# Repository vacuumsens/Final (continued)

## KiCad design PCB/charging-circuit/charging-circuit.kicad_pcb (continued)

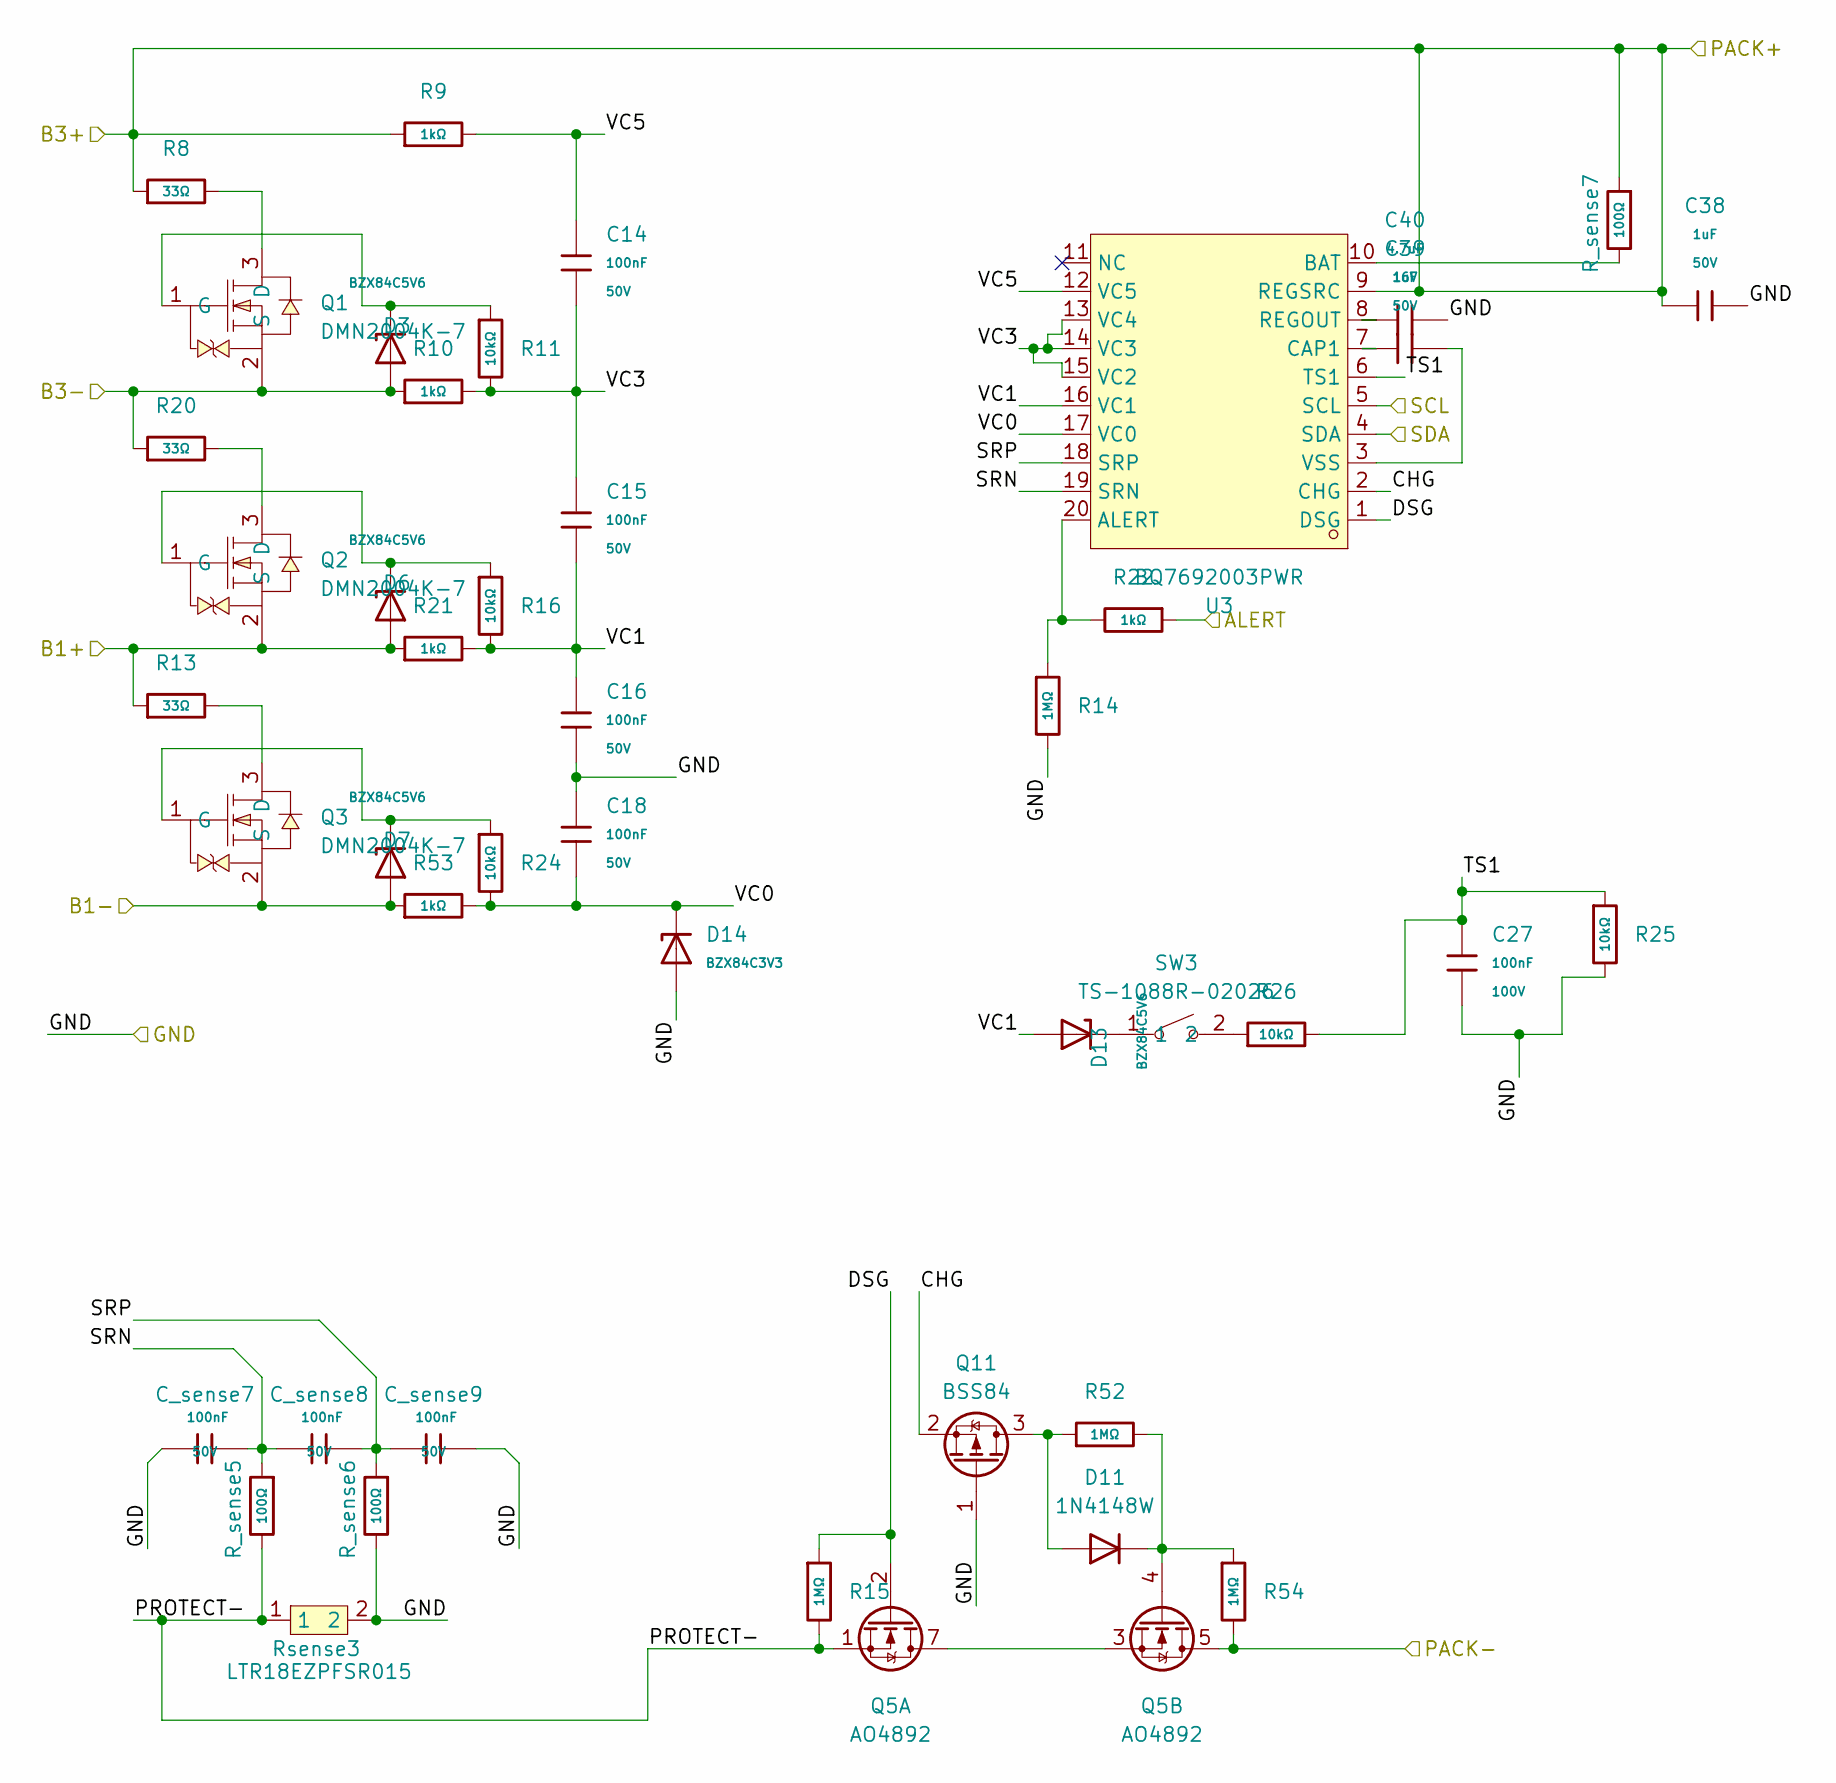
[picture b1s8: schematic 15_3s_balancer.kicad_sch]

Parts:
C14, C15, C16, C18: 100nF; C_0603; Voltage Rated 50V; Tolerance ±10%; Part CC0603KRX7R9BB104; LCSC C14663
C27: 100nF; C_0805; Voltage Rated 100V; Tolerance ±10%; Part CL21B104KCFNNNE; LCSC C28233
C38, C39: 1uF; C_0603; Voltage Rated 50V; Tolerance ±10%; Part CL10A105KB8NNNC; LCSC C15849
C40: 4.7uF; C_0603; Voltage Rated 16V; Tolerance ±10%; Part CL10A475KO8NNNC; LCSC C19666
C_sense7, C_sense8, C_sense9: 100nF; C_0603; Voltage Rated 50V; Tolerance ±10%; Part CC0603KRX7R9BB104; LCSC C14663
D3, D6, D7, D13: BZX84C5V6; D_SOT-23; Part BZX84C5V6; LCSC C19077469
D11: 1N4148W; D_SOD-123
D14: BZX84C3V3; D_SOT-23; Zener Voltage (Range) 3.1V~3.5V; Zener Voltage (Nom) 3.3V; Part BZX84C3V3; LCSC C19077467
Q1, Q2, Q3: DMN2004K-7; SOT-23-3_L3.0-W1.7-P0.95-LS2.9-BR; MPN DMN2004K-7; LCSC Part C75285
Q5: AO4892; SOIC-8_3.9x4.9mm_P1.27mm; LCSC Part C357830
Q11: BSS84; SOT-23; LCSC Part C82079
R8, R13, R20: 33Ω; R_0805; Overload Voltage (Max) 150V; Tolerance ±1%; Part 0805W8F330JT5E; LCSC C17634
R9, R10, R21, R22, R53: 1kΩ; R_0805; Overload Voltage (Max) 150V; Tolerance ±1%; Part 0805W8F1001T5E; LCSC C17513
R11, R16, R24, R25, R26: 10kΩ; R_0805; Overload Voltage (Max) 150V; Tolerance ±1%; Part 0805W8F1002T5E; LCSC C17414
R14: 1MΩ; R_0805; Overload Voltage (Max) 150V; Tolerance ±1%; Part 0805W8F1004T5E; LCSC C17514
R15, R52, R54: 1MΩ; R_0603; Overload Voltage (Max) 75V; Tolerance ±1%; Part 0603WAF1004T5E; LCSC C22935
R_sense5, R_sense6, R_sense7: 100Ω; R_0603; Overload Voltage (Max) 75V; Tolerance ±1%; Part 0603WAF1000T5E; LCSC C22775
Rsense3: LTR18EZPFSR015; R0612; LCSC Part C510175
SW3: TS-1088R-02026; SW-SMD_L3.9-W3.0-P4.45; LCSC Part C455280
U3: BQ7692003PWR; TSSOP-20_L6.5-W4.4-P0.65-LS6.4-BL; MPN BQ7692003PWR; LCSC Part C601650

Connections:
/3S Balancer/ALERT: R22.1
/3S Balancer/B1+: D6.1, Q2.2 (S), R13.1, R21.1; also elsewhere on the board
/3S Balancer/B3-: D3.1, Q1.2 (S), R10.1, R20.1; also elsewhere on the board
/3S Balancer/CHG: Q11.2 (S), U3.2 (CHG)
/3S Balancer/DSG: Q5.2 (G1), R15.1, U3.1 (DSG)
/3S Balancer/PROTECT-: Q5.1 (S1), R15.2, R_sense5.2, Rsense3.1
/3S Balancer/SRN: C_sense7.2, C_sense8.1, R_sense5.1, U3.19 (SRN)
/3S Balancer/SRP: C_sense8.2, C_sense9.1, R_sense6.1, U3.18 (SRP)
/3S Balancer/TS1: C27.1, R25.1, R26.2, U3.6 (TS1)
/3S Balancer/VC0: C18.2, D14.3, R24.2, R53.2, U3.17 (VC0)
/3S Balancer/VC1: C15.2, C16.1, D13.1, R16.2, R21.2, U3.16 (VC1)
/3S Balancer/VC3: C14.2, C15.1, R10.2, R11.2, U3.13 (VC4), U3.14 (VC3), U3.15 (VC2)
/3S Balancer/VC5: C14.1, R9.2, U3.12 (VC5)
/3S IC/BAT+: C38.1, R8.1, R9.1, R_sense7.1, U3.9 (REGSRC); also elsewhere on the board
/GND: C16.2, C18.1, C27.2, C38.2, C40.2, C_sense7.1, C_sense9.2, D7.1, D14.1, Q3.2 (S), Q5.5 (D2), Q5.6 (D2), Q11.1 (G), R14.2, R25.2, R53.1, R54.2, R_sense6.2, Rsense3.2; also elsewhere on the board
/GPIO2/SDA1: U3.4 (SDA); also elsewhere on the board
/GPIO3/SCL1: U3.5 (SCL); also elsewhere on the board
unnamed: D11.2 (A), Q11.3 (D), R52.1
unnamed: D11.1 (K), Q5.4 (G2), R52.2, R54.1
unnamed: D13.3, SW3.1
unnamed: Q1.3 (D), R8.2
unnamed: D3.3, Q1.1 (G), R11.1
unnamed: Q2.3 (D), R20.2
unnamed: D6.3, Q2.1 (G), R16.1
unnamed: Q3.3 (D), R13.2
unnamed: D7.3, Q3.1 (G), R24.1
unnamed: Q5.3 (S2), Q5.7 (D1), Q5.8 (D1)
unnamed: R26.1, SW3.2
unnamed: R14.1, R22.2, U3.20 (ALERT)
unnamed: R_sense7.2, U3.10 (BAT)
unnamed: C39.1, U3.7 (CAP1)
unnamed: C40.1, U3.8 (REGOUT)
unnamed: C39.2, U3.3 (VSS)

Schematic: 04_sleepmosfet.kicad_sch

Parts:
C65: 100nF; C_0603; Voltage Rated 50V; Tolerance ±10%; Part CC0603KRX7R9BB104; LCSC C14663
Q21, Q24, Q25, Q26: 2N7002; SOT-23-3_L2.9-W1.3-P1.90-LS2.4-BR; LCSC Part C8545
Q22, Q27, Q28: CJQ4435; SOP-8_L5.0-W4.0-P1.27-LS6.2-BL; LCSC Part C114076
R6: 3362P-1-204; RES-ADJ-TH_3P-L7.1-W6.9-P2.50-L_3362P; MPN 3362P-1-204; LCSC Part C118941
R37, R38, R41, R43, R47: 10kΩ; R_0603; Overload Voltage (Max) 75V; Tolerance ±1%; Part 0603WAF1002T5E; LCSC C25804
R46, R48, R49: 100kΩ; R_0603; Overload Voltage (Max) 75V; Tolerance ±1%; Part 0603WAF1003T5E; LCSC C25803
RPROG9, RPROG10: 1kΩ; R_0603; Overload Voltage (Max) 75V; Tolerance ±1%; Part 0603WAF1001T5E; LCSC C21190
U19: TPL5110DDCT; TSOT-23-6_L2.9-W1.6-P0.95-LS2.8-BR; LCSC Part C125830

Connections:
/DSUB+RS232/DSUB3.3V: Q22.1 (S), Q22.2 (S), Q22.3 (S), R43.2, R46.1, U19.1 (VDD), U19.6 (EN/ONE_SHOT); also elsewhere on the board
/DSUB+RS232/DSUB12V: Q28.5 (D), Q28.6 (D), Q28.7 (D), Q28.8 (D), R49.2; also elsewhere on the board
/GND: C65.2, Q21.2 (S), Q24.2 (S), Q25.2 (S), Q26.2 (S), R6.2, R37.2, R38.2, R41.1, R49.1, RPROG9.2, RPROG10.2, U19.2 (GND); also elsewhere on the board
/GPIO23: Q21.1 (G), R41.2; also elsewhere on the board
/LM2596 3V3 BUCK/LM2596_VIN: Q27.1 (S), Q27.2 (S), Q27.3 (S), Q28.1 (S), Q28.2 (S), Q28.3 (S), R47.2, R48.2; also elsewhere on the board
/SLEEPMOSFET/5EN: Q27.5 (D), Q27.6 (D), Q27.7 (D), Q27.8 (D), RPROG10.1; also elsewhere on the board
/SLEEPMOSFET/SLPDRV: Q24.1 (G), Q25.1 (G), R38.1, U19.5 (DRV)
/SLEEPMOSFET/SLPSIG: C65.1, Q22.5 (D), Q22.6 (D), Q22.7 (D), Q22.8 (D), R37.1, RPROG9.1, U19.4 (DONE)
unnamed: Q21.3 (D), Q22.4 (G), R43.1
unnamed: Q24.3 (D), Q26.1 (G), R46.2
unnamed: Q25.3 (D), Q27.4 (G), R47.1
unnamed: Q26.3 (D), Q28.4 (G), R48.1
unnamed: R6.3, U19.3 (DELAY/M_DRV)

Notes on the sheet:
n, pmos driver for enable pin of lmk2596 5 volts
Battery can still charge while timer off DONE = rising edge, turn off mosfet and circuit power for sleep timer DONE = low, circuit power on
timing resistor 20k for around 2 minutes
Module: SLEEPMOSFET Move the matching boxed circuit here from charging-circuit.flat-backup.kicad_sch. Use global labels or hierarchical pins for any net that must connect outside this sheet. Suggested nets: SLEEPGND, SLEEPSIG, SLEEPVSYS
n, pmos driver for raspi to tpl5110 side (3.3 Volts NOT 12)
n,n,pmos driver for 12Volts (directly from battery)

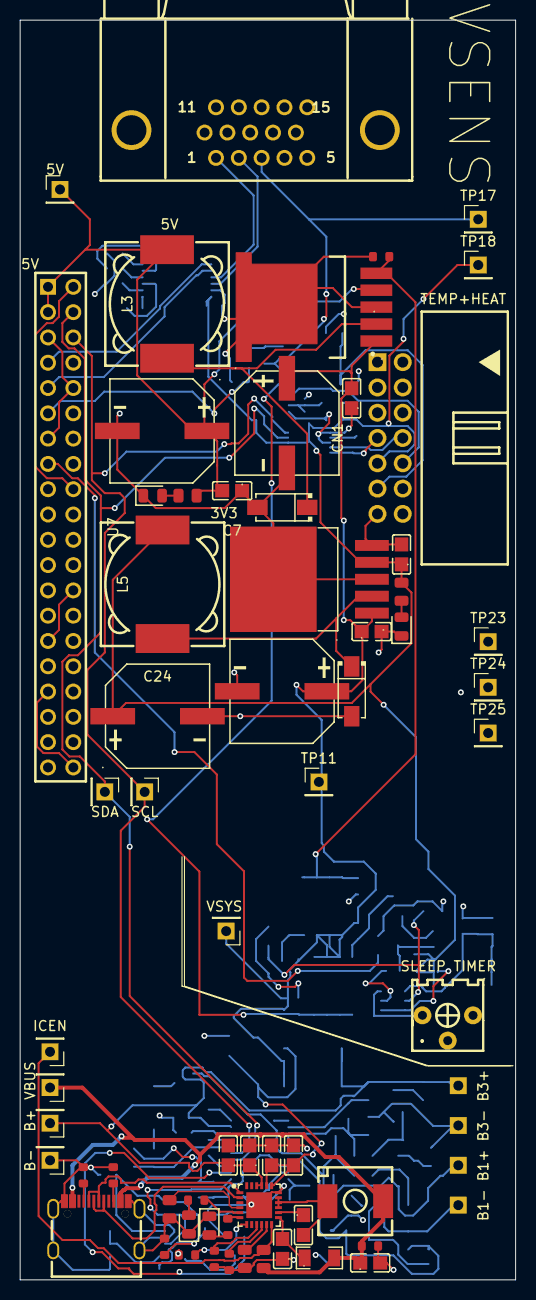
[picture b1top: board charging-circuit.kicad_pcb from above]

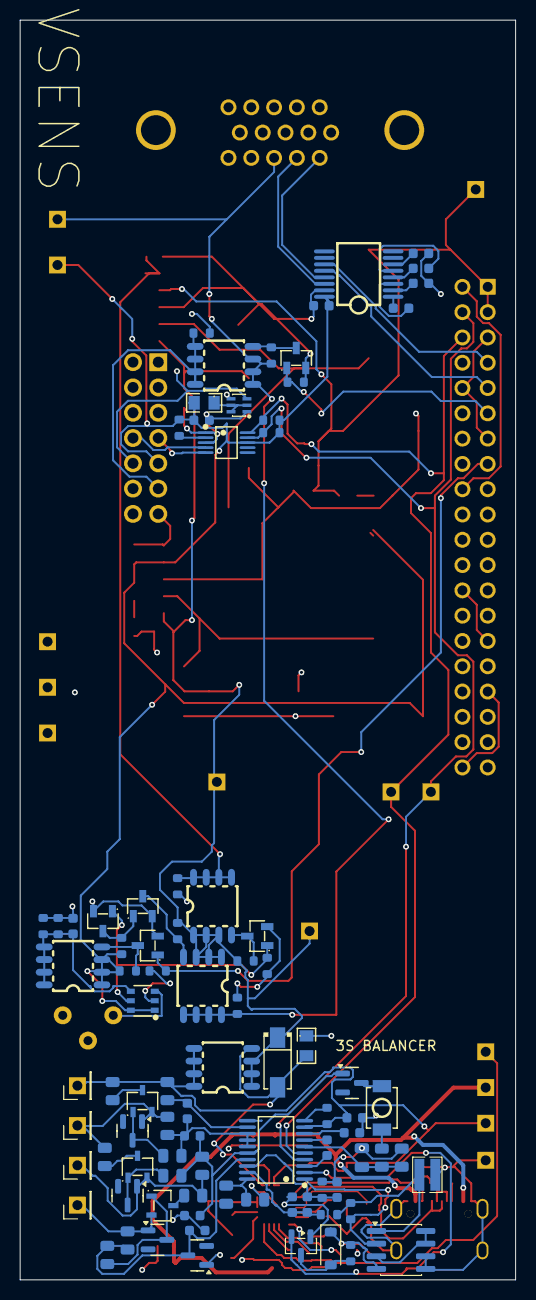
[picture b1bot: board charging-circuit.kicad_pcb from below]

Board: 4 copper layers, 49.8 x 126.5 mm, 150 parts (88 on the bottom side), 87 nets.

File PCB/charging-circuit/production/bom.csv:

Designator,Footprint,Quantity,Value,LCSC Part #
"_15, _14, _13, _12, _11, _10, _9, _8, _7, _6, _5, _4, _3, _2, ",,15,,
"C10, C11, C12, C8",C0805,4,10uf,C84416
"C13, C14, C15, C16, C18, C22, C29, C33, C35, C36, C65, C_SENSE7, C_SENSE8, C_SENSE9",C_0603,14,100nF,C14663
"C19, C2, C3, C6, C7",C0805,5,100nf,C1711
C21,CAP-SMD_BD10.0-L10.3-W10.3-FD,1,330uf,C19606
"C23, C24, C25",CAP-SMD_BD10.0-L10.3-W10.3-LS11.0-FD,3,470uf,C3351
C27,C_0805,1,100nF,C28233
"C38, C39",C_0603,2,1uF,C15849
"C4, C5",C0805,2,22uf,C45783
C40,C_0603,1,4.7uF,C19666
CN1,IDC-TH_14P-P2.54_ZHOURI_DC3-2.54-14PAL,1,DC3-2.54-14PAL,C5156673
"D1, D2, D5",SMA_L4.4-W2.8-LS5.4-R-RD,3,SS54_C22452,C22452
"D10, D12, D9",D_0805,3,Green,C2297
D11,D_SOD-123,1,1N4148W,
"D13, D3, D6, D7",D_SOT-23,4,BZX84C5V6,C19077469
D14,D_SOT-23,1,BZX84C3V3,C19077467
D8,D_0805,1,Red,C84256
DSUB2,DSUB-TH_DS1038-15FBNSIA74-0CC,1,DS1038-15FBNSIA74-0CC,C75754
L1,IND-SMD_L7.1-W6.5-P5.60,1,SPM6530T-2R2M,C76855
"L3, L5",IND-SMD_L12.3-W12.3,2,SMDRI127-330MT,C9400
"Q1, Q2, Q3",SOT-23-3_L3.0-W1.7-P0.95-LS2.9-BR,3,DMN2004K-7,C75285
Q11,SOT-23,1,BSS84,C82079
"Q14, Q21, Q24, Q25, Q26",SOT-23-3_L2.9-W1.3-P1.90-LS2.4-BR,5,2N7002,C8545
"Q17, Q18, Q22, Q27, Q28",SOP-8_L5.0-W4.0-P1.27-LS6.2-BL,5,CJQ4435,C114076
Q23,SOT-363-6_L2.2-W1.3-P0.65-LS2.1-BL,1,currentmirror,C41375126
Q5,SOIC-8_3.9x4.9mm_P1.27mm,1,AO4892,C357830
R1,R0805,1,0805W8F2553T5E,C17578
"R10, R21, R22, R53, R9",R_0805,5,1kΩ,C17513
"R11, R16, R24, R25, R26",R_0805,5,10kΩ,C17414
R12,R_0805,1,62kΩ,C17783
"R13, R20, R8",R_0805,3,33Ω,C17634
R14,R_0805,1,1MΩ,C17514
"R15, R52, R54",R_0603,3,1MΩ,C22935
"R18, R19",R_0805,2,51kΩ,C17737
"R2, R3",R_0805,2,4.7kΩ,C17673
"R31, R32, R33, R40, R44, R45",R_0603,6,5.1kΩ,C23186
"R37, R38, R39, R41, R43, R47, R50",R_0603,7,10kΩ,C25804
R4,R1206,1,0.5ohm,C25340
"R46, R48, R49, R51",R_0603,4,100kΩ,C25803
R5,R0805,1,100k,C25611
R6,RES-ADJ-TH_3P-L7.1-W6.9-P2.50-L_3362P,1,3362P-1-204,C118941
"RPROG10, RPROG11, RPROG12, RPROG13, RPROG14, RPROG15, RPROG8, RPROG9",R_0603,8,1kΩ,C21190
RSENSE3,R0612,1,LTR18EZPFSR015,C510175
"R_SENSE5, R_SENSE6, R_SENSE7",R_0603,3,100Ω,C22775
SW3,SW-SMD_L3.9-W3.0-P4.45,1,TS-1088R-02026,C455280
TP10,PinHeader_1x01_P2.54mm_Vertical,1,VSYS,
TP15,PinHeader_1x01_P2.54mm_Vertical,1,SDA,
TP16,PinHeader_1x01_P2.54mm_Vertical,1,SCL,
TP17,PinHeader_1x01_P2.54mm_Vertical,1,12VOUT,
TP18,PinHeader_1x01_P2.54mm_Vertical,1,3V3,
TP19,PinHeader_1x01_P2.54mm_Vertical,1,TX,
"TP2, TP3, TP4, TP5, TP9",PinHeader_1x01_P2.54mm_Vertical,5,TestPoint,
TP20,PinHeader_1x01_P2.54mm_Vertical,1,RX,
TP21,PinHeader_1x01_P2.54mm_Vertical,1,5V,
TP6,PinHeader_1x01_P2.54mm_Vertical,1,BAT-,
TP7,PinHeader_1x01_P2.54mm_Vertical,1,Bat+,
TP8,PinHeader_1x01_P2.54mm_Vertical,1,VBUS,
U1,VQFN-24_L4.0-W4.0-P0.50-BL-EP2.5,1,IP2326,C2832094
U10,SSOP-16_L6.2-W5.3-P0.65-LS7.8-BL,1,MAX3232CDBR,C7257
U12,MSOP-10_L3.0-W3.0-P0.50-LS5.0-BL,1,ADS1115IDGSR,C37593
U19,TSOT-23-6_L2.9-W1.6-P0.95-LS2.8-BR,1,TPL5110DDCT,C125830
U2,TDFN-8_L2.0-W2.0-P0.50-BL-EP1.2,1,MAX17048G+T10,C2682616
U3,TSSOP-20_L6.5-W4.4-P0.65-LS6.4-BL,1,BQ7692003PWR,C601650
U4,TO-263-5_L10.2-W8.6-P1.70-LS14.4-TL,1,LM2596SX-3.3,C5186052
U6,TO-263-5_L10.2-W8.9-P1.70-TL,1,LM2596SX-5.0/NOPB,C10002
U7,HDR-TH_40P-P2.54-V-F-R2-C20-S2.54,1,2.54-2*20,C2977589
USBC1,USB-C_SMD-TYPE-C-31-M-12_1,1,TYPE-C-31-M-12,C165948

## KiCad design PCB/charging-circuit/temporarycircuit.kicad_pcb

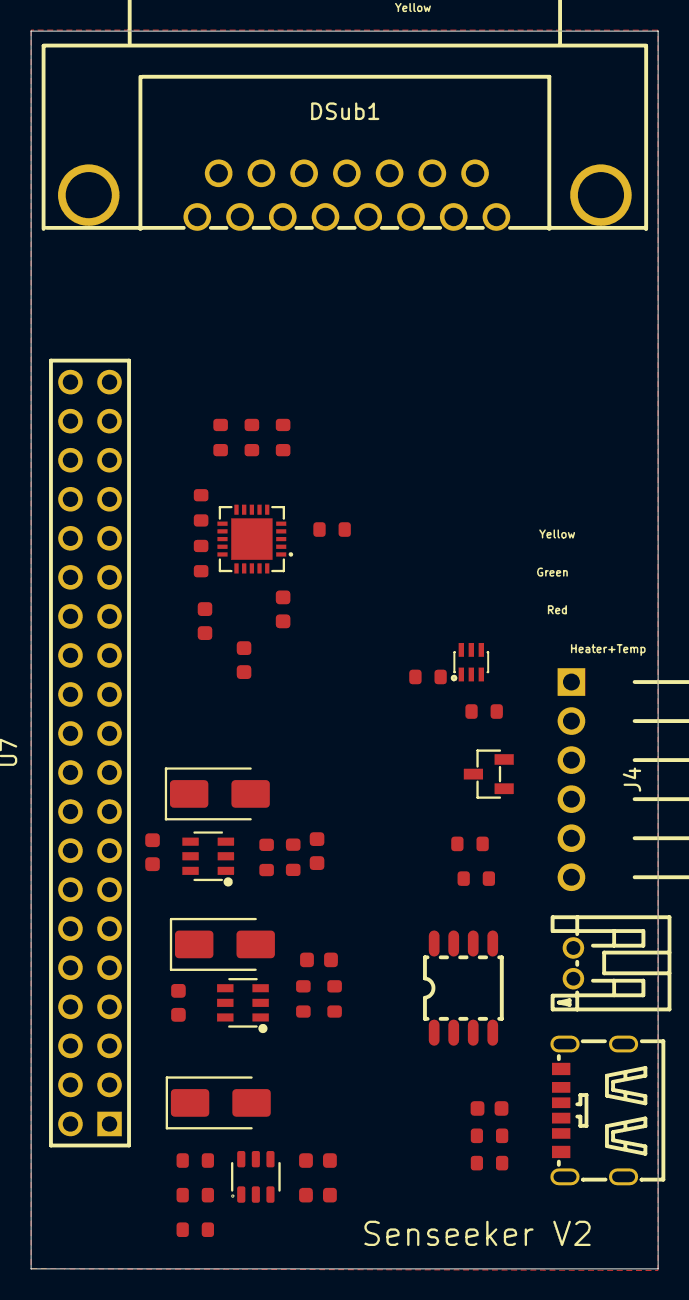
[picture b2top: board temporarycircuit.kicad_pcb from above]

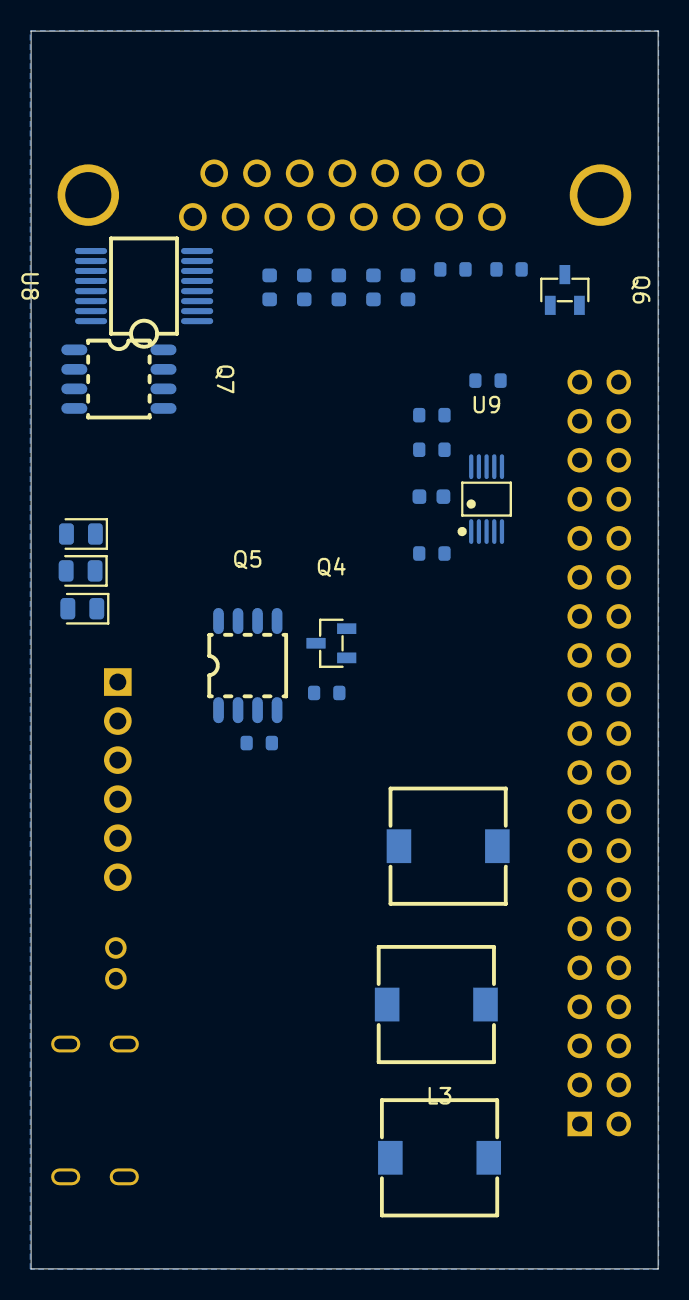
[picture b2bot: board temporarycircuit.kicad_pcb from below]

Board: 2 copper layers, 40.8 x 80.5 mm, 70 parts (26 on the bottom side), 53 nets, no tracks yet.

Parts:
C1, C6: 4.7uF; C_0603
C2, C12, C17, C18, C19, C20, C21: 100nF; C_0603
C3, C4, C5, C7, C10, C11: 22uF; C_0603
C8: 10uF; C_0603
D1: Red; D_0805
D2: Yellow; D_0805
D3: Green; D_0805
D4, D5, D6: SS34; D_SMA
DSub1: DS1037-15FNAKT74-0CC; DSUB-TH_DS1037-15FNAKT74-0CC
J1: USB_C_Receptacle_PowerOnly_6P; TYPE-C-SMD_TYPE-C-6P
J4: Heater+TempPins; HDR-TH_6P-P2.54-H-M-W10.0
L1, L2, L3: 22uH; IND-SMD_L7.5-W7.5
Q1, Q4, Q6: 2N7002; SOT-23-3_L2.9-W1.3-P1.90-LS2.4-BR
Q2, Q5, Q7: CJQ4435; SOP-8_L5.0-W4.0-P1.27-LS6.2-BL
Q3: currentmirror; SOT-363-6_L2.2-W1.3-P0.65-LS2.1-BL
R1, R2, R12, R13, R21: 5.1kΩ; R_0603
R3: 3kΩ; R_0603
R4: 20kΩ; R_0603
R5, R14, R15, R16: 10kΩ; R_0603
R6, R7, R11: 470Ω; R_0603
R8: 91kΩ; R_0603
R9: 4.7kΩ; R_0603
R10: 22kΩ; R_0603
R18: 6.8kΩ; R_0603
R19: 2kΩ; R_0603
R20: 2.2kΩ; R_0603
R22: 100Ω; R_0603
R23: 240kΩ; R_0603
RPROG1, RPROG4, RPROG5, RPROG6: 1kΩ; R_0603
RPROG3: 10kΩ; R_0603
U2, U3, U6: MT3608; SOT-23-6_L2.9-W1.6-P0.95-LS2.8-BL
U4: MCP73871; QFN-20_L4.0-W4.0-P0.5-BL-EP
U5: Battery Input; CONN-TH_S2B-PH-K-S-GW
U7: 2.54-2*20; HDR-TH_40P-P2.54-V-F-R2-C20-S2.54
U8: MAX3232CDBR; SSOP-16_L6.2-W5.3-P0.65-LS7.8-BL
U9: ADS1115IDGSR; MSOP-10_L3.0-W3.0-P0.50-LS5.0-BL

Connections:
/3.3V: C11.2, C21.1, D6.1, Q5.1 (S), Q5.2 (S), Q5.3 (S), R16.2, R18.1, U8.16 (VCC)
/5 Vout: C4.2, D5.1, R10.1, U7.2, U7.4
/12V: C3.2, D4.1, Q2.1 (S), Q2.2 (S), Q2.3 (S), Q7.1 (S), Q7.2 (S), Q7.3 (S), R8.1, R14.2, R15.2
/A0: J4.5, U9.4 (AIN0)
/A1: J4.6, U9.5 (AIN1)
/Address: R22.2, U9.1 (ADDR)
/GPIO3/SCL1: R12.2, R21.2, U7.5, U9.9 (SDA), U9.10 (SCL)
/GPIO14/TXD0: U7.8, U8.11 (DIN1)
/GPIO15/RXD0: U7.10, U8.12 (ROUT1)
/GPIO18/PCM.CLK: Q1.1 (G), U7.12
/GPIO23: Q6.1 (G), U7.16
/GPIO24: Q4.1 (G), U7.18
/Temp3.3V: C12.1, J4.4, Q5.5 (D), Q5.6 (D), Q5.7 (D), Q5.8 (D), R4.1, R12.1, R13.1, R21.1, RPROG4.1, U9.8 (VDD)
/UART_RX_13V: DSub1.1, U8.13 (RIN1)
/UART_TX_13V: DSub1.2, U8.14 (DOUT1)
/VSYS: C5.1, C6.2, C7.1, C10.1, L1.1, L2.1, L3.1, U2.4 (EN), U2.5 (IN), U3.4 (EN), U3.5 (IN), U4.1 (OUT), U4.20 (OUT), U6.4 (EN), U6.5 (IN)
/base: Q3.2 (B), Q3.5 (B), Q3.6 (C), R23.2
/raspi3.3V: U7.1, U7.17
GND: C1.1, C2.2, C3.1, C4.1, C5.2, C6.1, C7.2, C8.1, C10.2, C11.1, C12.2, C17.2, C18.2, C21.2, DSub1.4, J1.A12 (GND), J1.B12 (GND), J1.S1 (SHIELD), J4.1, Q1.2 (S), Q3.1 (E), Q3.4 (E), Q4.2 (S), Q6.2 (S), R1.2, R2.2, R3.2, R5.2, R9.2, R19.2, R22.1, RPROG1.1, RPROG3.2, RPROG4.2, RPROG5.2, RPROG6.2, U2.2 (GND), U3.2 (GND), U4.10 (V_{SS}), U4.11 (V_{SS}), U4.21 (V_{SS}), U5.2, U6.2 (GND), U7.6, U7.9, U7.14, U7.20, U7.25, U7.30, U7.34, U7.39, U8.15 (GND), U9.3 (GND)
unnamed: D1.1, R7.1
unnamed: D2.1, R11.1
unnamed: D3.1, R6.1
unnamed: DSub1.3, Q7.5 (D), Q7.6 (D), Q7.7 (D), Q7.8 (D), RPROG6.1
unnamed: J1.A5 (CC1), R1.1
unnamed: J1.B5 (CC2), R2.1
unnamed: J4.2, Q2.5 (D), Q2.6 (D), Q2.7 (D), Q2.8 (D), RPROG5.1
unnamed: J4.3, Q3.3 (C)
unnamed: Q1.3 (D), Q2.4 (G), R14.1
unnamed: Q4.3 (D), Q5.4 (G), R16.1
unnamed: Q6.3 (D), Q7.4 (G), R15.1
unnamed: R18.2, R20.1
unnamed: R4.2, R23.1
unnamed: R3.1, R10.2, U2.3 (FB)
unnamed: D5.2, L1.2, U2.1 (SW)
unnamed: R8.2, R9.1, U3.3 (FB)
unnamed: D4.2, L2.2, U3.1 (SW)
unnamed: RPROG1.2, U4.13 (PROG1)
unnamed: RPROG3.1, U4.12 (PROG3)
unnamed: R7.2, U4.8 (STAT1/~LBO)
unnamed: R6.2, U4.7 (STAT2)
unnamed: R5.1, U4.5 (THERM)
unnamed: C1.2, U4.14 (V_{BAT}), U4.15 (V_{BAT}), U4.16 (V_{BAT_SENSE}), U5.1
unnamed: R11.2, U4.6 (~PG)
unnamed: R19.1, R20.2, U6.3 (FB)
unnamed: D6.2, L3.2, U6.1 (SW)
unnamed: C20.1, U8.1 (C1+)
unnamed: C20.2, U8.3 (C1-)
unnamed: C19.1, U8.4 (C2+)
unnamed: C19.2, U8.5 (C2-)
unnamed: C18.1, U8.2 (V+)
unnamed: C17.1, U8.6 (V-)
unnamed: R13.2, U9.2 (ALERT/RDY)
VBUS: C2.1, C8.2, D1.2, D2.2, D3.2, J1.A9 (VBUS), J1.B9 (VBUS), U4.2 (VPCC), U4.3 (SEL), U4.4 (PROG2), U4.9 (~TE), U4.17 (CE), U4.18 (IN), U4.19 (IN)

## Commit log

2026-06-02 final
2026-06-03 Add Client Image
2026-06-03 Add comprehensive Client module README
2026-06-03 Add comprehensive Server module README
2026-06-03 Add STEP file of CAD
2026-06-05 Delete PossibleChangesNotes.txt
    Outdated Notes
2026-06-05 Delete User Manual.md
    Unused Manual
2026-06-06 restore
2026-06-08 convert to md file and add more troubleshooting details
